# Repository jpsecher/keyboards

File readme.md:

# Custom Keyboard

Goals
- Good ergonomics
- Good for programming
- No drivers
- Configurable
- Use standard components where possible

On the ergonomics side, the initial design will be a pseudo-split staggered-column because it follows the natural physiology of the hands, and because I only need to make one or two for myself.  I want to make a PCB for the keyboard, so it seems to convoluted to go all the way to curved surfaces (eg. wells).  With a PCB, I can also support hot-swappable keys, which makes it possible to try out different spring weights for the individual fingers (like the [Absolem](https://zealot.hu/absolem/)).  And no stabilisers should be needed because the keys should just be where your finger naturally land, and therefore there should be no need for large 2U keys.  For the thumb keys, size 1.5U is probably sufficient.

Keys that need to be hold down while pressing other keys should only be operated by strong fingers.  So all modifier keys and layer shifting should probably be in the thumbs area, where it will be most comfortable to hold down a keys (as opposed to tapping the key).  But some modifier keys need to be hold down together, so these modifiers then need to be on opposite sides, using both thumbs at the same time.  

Good ergonomics with no curvatures then means that the number of keys must be limited to avoid stretching the fingers too much.  Which means that the keyboard needs to have several layers to accommodate all the ASCII characters used in programming, as well as the various European letters I use daily.  I am toying with the idea of using the thumb keys exclusively for layer-shift and control keys.

The keyboard should use standard hot-swappable Cherry MX keys.  And to ease experimentation, I will start out with DSA profile key caps.

## Layers

Contexts:

  1.  Programming (standard languages) in non-modal text editor.
  1.  Documentation (Markdown) in non-modal editor.
  1.  Terminal (shell) operations.
  1.  Window manager navigation.
  1.  Music control (easy identification of Play/Pause key at a glance)

And:

- Function keys are important in many of the applications I use.
- Editors usually inserts ending parenthesis/brace/bracket automatically.
- I don't care about RGB LEDs, as long as I can turn them off.
- I occasionally use Nordic/German/Greek letters when writing text.
- I want modifiers and layer keys on thumbs, and they should stay in the same place as much as possible.

Also, I prefer that each group of keys follow the traditional QWERTY layout, simply because it makes switching between keyboards less stressful.

## Keyboards in this repository

- [Acacia](acacia/): a pseudo-split 40 key column-staggered keyboard

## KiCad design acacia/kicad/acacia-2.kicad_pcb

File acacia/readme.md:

# Acacia keyboard

A custom built mechanical keyboard with just 38 keys plus two extra media keys.

The [layout](acacia.pdf) uses three layers.  One for alphas, one for navigation/function keys, and one for symbols/numpad.

The thumb home keys double as layer switches and tab/space.  The lower thumb keys are one-shot shift keys.

The Escape key is a [Layer Lock](https://getreuer.info/posts/keyboards/layer-lock) on both upper layers, which eliminates the strain of holding down the thumb for prolonged navigation and number punching.  And it makes it possible to move one hand to a trackball while using the other hand for mouse buttons.

The lower home row (Z, X, C, V) doubles as modifiers (AltGr, GUI, Alt, Control), and these functions are mirrored on the other hand (M, comma, period, quote).  This mirroring of modifiers is carried through on both other layers.

If used on macOS, then the Control and GUI (Command) keys should be swapped at the OS level.

As seen on the picture, the current layout for the alphas is [Minimak-6](http://www.minimak.org/), and it works very well with the already relocated T and Y keys on Acacia.  It is pretty close to standard QWERTY, so changing between the two should not be a problem.

## Improvements

- Remove the now unused lower thumb keys.
- Adjust the thumb keys slightly to make sure that key caps of any reasonable size do not collide.  Also, the thumb home key could be a little less tilted, and the whole bock moved a little further towards the middle.
- Align Q and P keys with ring finger use (instead of pinky use), or simply tilt the pinky columns the same as the ring finger column.
- Include a trackball (as alluded to in the pictures).  Unfortunately the ATmega32U2 used in the build does not have built-in I2C communication, so unless the controller is upgraded to eg. ATmega32U4, the communication has to be done brute-force through some of the five unused GPIO pins.
- Make a proper (wooden?) case.
- Shielding for the PCB.
- Layer status output, eg. through LEDs.

## Alternatives

- After finishing the prototypes, I discovered this repo: https://github.com/AlaaSaadAbdo/battoota/

## Version 2

The TM040040 trackpad needs the R1 (470k) resistor removed to use I2C and the R7 (0?) & R8 (0?) resistors removed for 5V.  The flex cable needed is 05-12-D-0050-A or another cable with contacts on oposite sides.

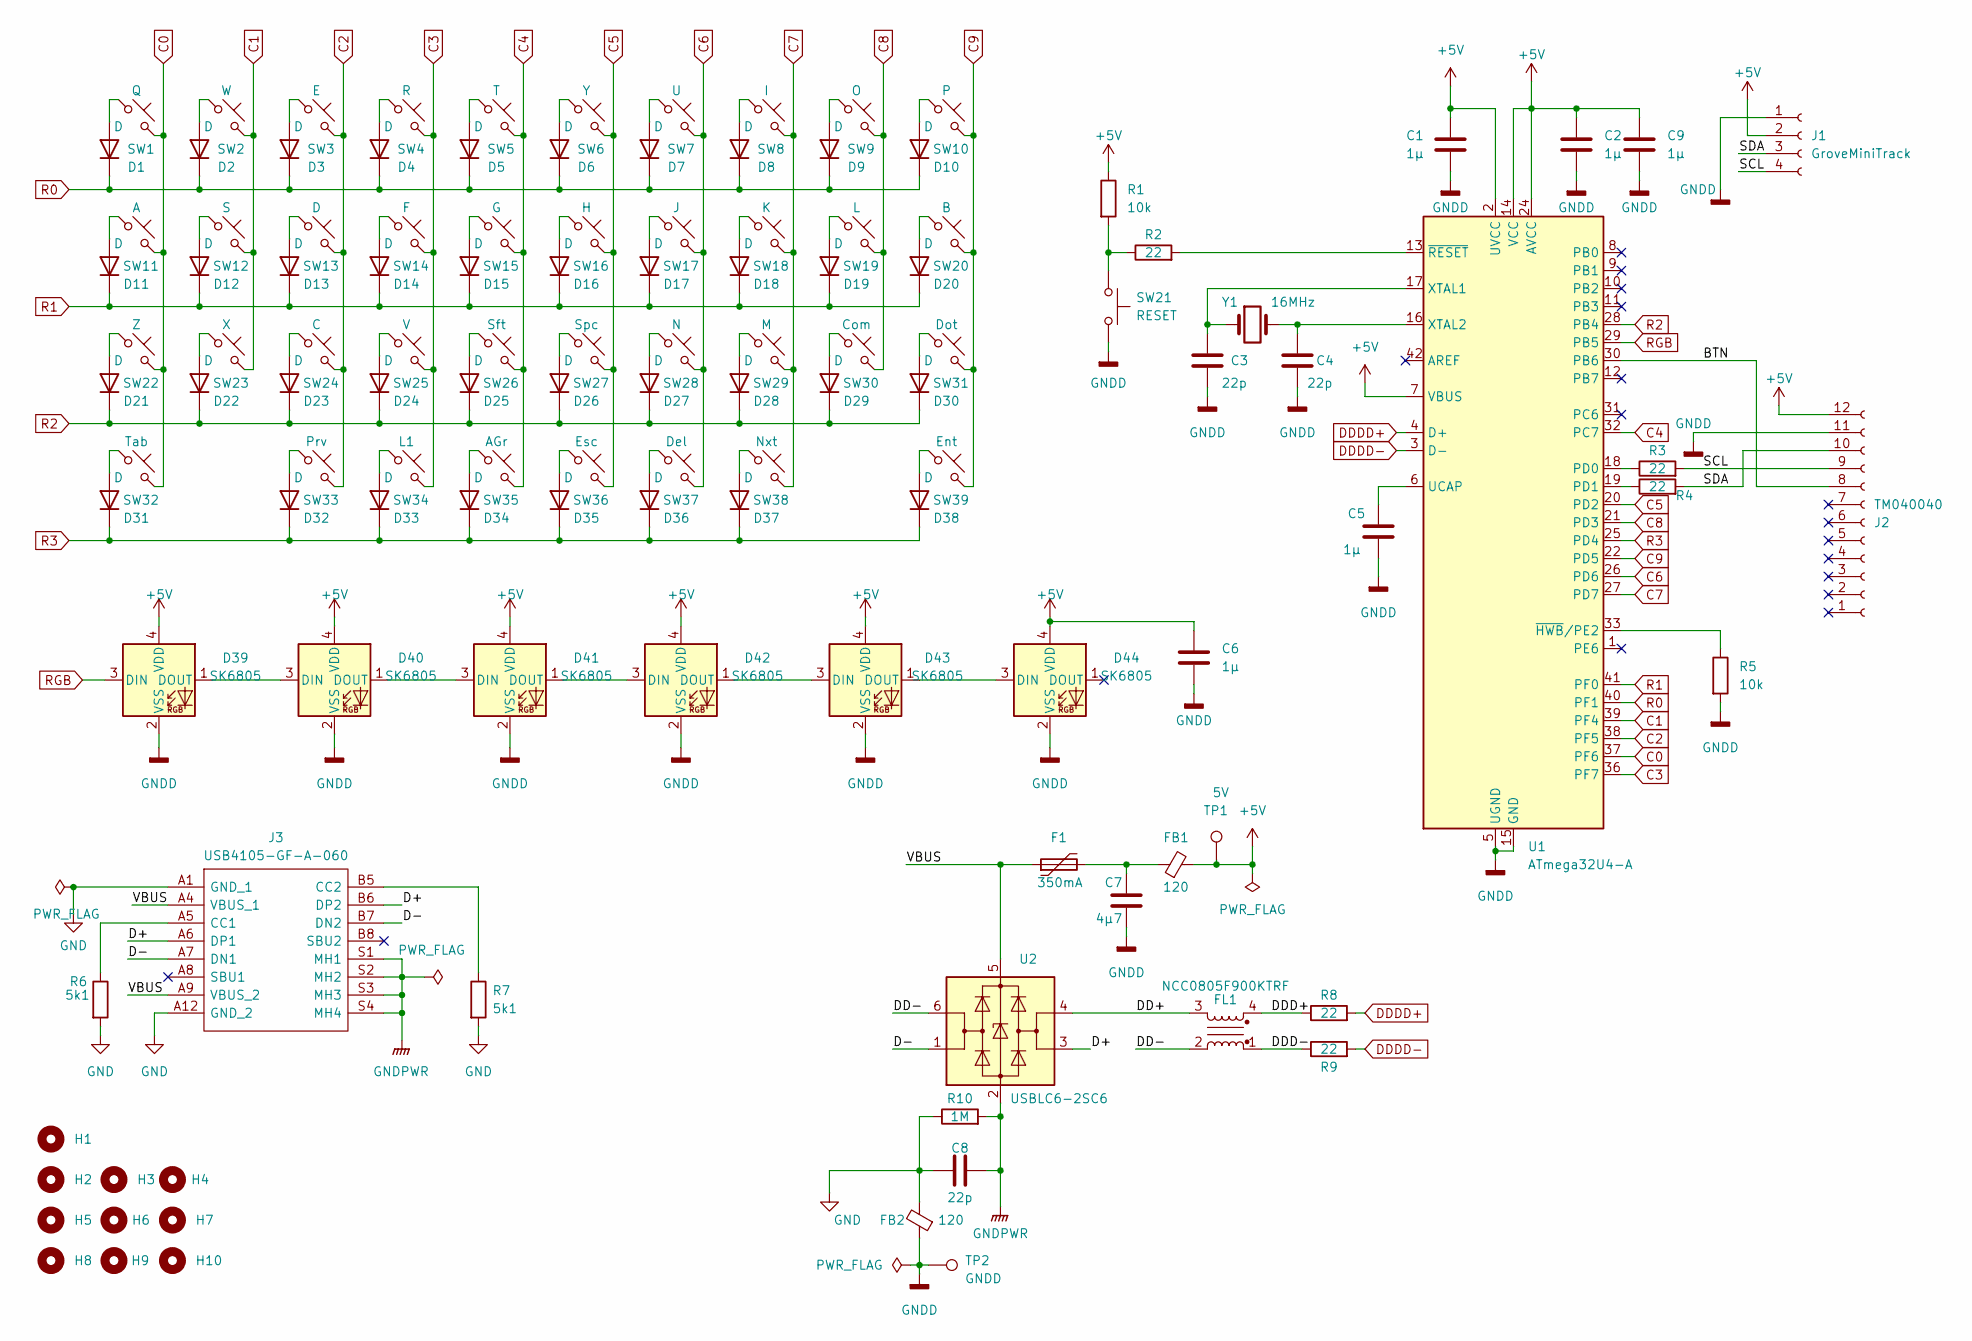
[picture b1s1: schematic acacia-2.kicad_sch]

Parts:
C1: 1µ; C_1206_3216Metric_Pad1.33x1.80mm_HandSolder
C2, C5, C6, C9: 1µ; C_0805_2012Metric_Pad1.18x1.45mm_HandSolder
C3, C4, C8: 22p; C_0805_2012Metric_Pad1.18x1.45mm_HandSolder
C7: 4µ7; C_0805_2012Metric_Pad1.18x1.45mm_HandSolder
D1, D2, D3, D4, D5, D6, D7, D8, D9, D10, D11, D12, D13, D14, D15, D16, D17, D18, D19, D20, D21, D22, D23, D24, D25, D26, D27, D28, D29, D30, D31, D32, D33, D34, D35, D36, D37, D38: D; D_0805_2012Metric_Pad1.15x1.40mm_HandSolder
D39, D40, D41, D42, D43, D44: SK6805; LED_SK6812_EC15_1.5x1.5mm
F1: 350mA; R_1206_3216Metric_Pad1.30x1.75mm_HandSolder
FB1, FB2: 120; R_0805_2012Metric_Pad1.20x1.40mm_HandSolder
FL1: NCC0805F900KTRF; L_CommonModeChoke_Coilcraft_0805USB
H1, H2, H3, H4, H5, H6, H7, H8, H9, H10: MountingHole; MountingHole_3.2mm_M3
J1: GroveMiniTrack; JST_XA_B04B-XASK-1-A_1x04_P2.50mm_Vertical
J2: TM040040; Hirose_FH12-12S-0.5SH_1x12-1MP_P0.50mm_Horizontal
J3: USB4105-GF-A-060; GCT_USB4105-GF-A; Mouser Part Number 640-USB4500030A
R1, R5: 10k; R_0805_2012Metric_Pad1.20x1.40mm_HandSolder
R2, R3, R4, R8, R9: 22; R_0805_2012Metric_Pad1.20x1.40mm_HandSolder
R6, R7: 5k1; R_0805_2012Metric_Pad1.20x1.40mm_HandSolder
R10: 1M; R_0805_2012Metric_Pad1.20x1.40mm_HandSolder
SW1: Q; MX-Hotswap-1U
SW2: W; MX-Hotswap-1U
SW3: E; MX-Hotswap-1U
SW4: R; MX-Hotswap-1U
SW5: T; MX-Hotswap-1U
SW6: Y; MX-Hotswap-1U
SW7: U; MX-Hotswap-1U
SW8: I; MX-Hotswap-1U
SW9: O; MX-Hotswap-1U
SW10: P; MX-Hotswap-1U
SW11: A; MX-Hotswap-1U
SW12: S; MX-Hotswap-1U
SW13: D; MX-Hotswap-1U
SW14: F; MX-Hotswap-1U
SW15: G; MX-Hotswap-1U
SW16: H; MX-Hotswap-1U
SW17: J; MX-Hotswap-1U
SW18: K; MX-Hotswap-1U
SW19: L; MX-Hotswap-1U
SW20: B; MX-Hotswap-1U
SW21: RESET; SW_SPST_EVQQ2
SW22: Z; MX-Hotswap-1U
SW23: X; MX-Hotswap-1U
SW24: C; MX-Hotswap-1U
SW25: V; MX-Hotswap-1U
SW26: Sft; MX-Hotswap-1.5U
SW27: Spc; MX-Hotswap-1.5U
SW28: N; MX-Hotswap-1U
SW29: M; MX-Hotswap-1U
SW30: Com; MX-Hotswap-1U
SW31: Dot; MX-Hotswap-1U
SW32: Tab; MX-Hotswap-1.5U
SW33: Prv; MX-Hotswap-1.5U
SW34: L1; MX-Hotswap-1U
SW35: AGr; MX-Hotswap-1.5U
SW36: Esc; MX-Hotswap-1.5U
SW37: Del; MX-Hotswap-1U
SW38: Nxt; MX-Hotswap-1.5U
SW39: Ent; MX-Hotswap-1.5U
TP1: 5V; TestPoint_Pad_D1.5mm
TP2: GNDD; TestPoint_Pad_D1.5mm
U1: ATmega32U4-A; TQFP-44_10x10mm_P0.8mm
U2: USBLC6-2SC6; SOT-23-6
Y1: 16MHz; Crystal_SMD_HC49-SD

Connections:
+5V: C1.1, C2.1, C6.1, C9.1, D39.4 (VDD), D40.4 (VDD), D41.4 (VDD), D42.4 (VDD), D43.4 (VDD), D44.4 (VDD), FB1.2, J1.2, J2.12, R1.1, TP1.1, U1.2 (UVCC), U1.7 (VBUS), U1.14 (VCC), U1.24 (AVCC), U1.34 (VCC), U1.44 (AVCC)
/BTN: J2.8, U1.30 (PB6)
/D+: J3.A6 (DP1), J3.B6 (DP2), U2.3 (I/O2)
/D-: J3.A7 (DN1), J3.B7 (DN2), U2.1 (I/O1)
/DD+: FL1.3, U2.4 (I/O2)
/DD-: FL1.2, U2.6 (I/O1)
/DDD+: FL1.4, R8.1
/DDD-: FL1.1, R9.1
/SCL: J1.4, J2.9, R3.2
/SDA: J1.3, J2.10, R4.2
/VBUS: F1.1, J3.A4 (VBUS_1), J3.A9 (VBUS_2), U2.5 (VBUS)
C0: SW1.2, SW11.2, SW22.2, SW32.2, U1.37 (PF6)
C1: SW2.2, SW12.2, SW23.2, U1.39 (PF4)
C2: SW3.2, SW13.2, SW24.2, SW33.2, U1.38 (PF5)
C3: SW4.2, SW14.2, SW25.2, SW34.2, U1.36 (PF7)
C4: SW5.2, SW15.2, SW26.2, SW35.2, U1.32 (PC7)
C5: SW6.2, SW16.2, SW27.2, SW36.2, U1.20 (PD2)
C6: SW7.2, SW17.2, SW28.2, SW37.2, U1.26 (PD6)
C7: SW8.2, SW18.2, SW29.2, SW38.2, U1.27 (PD7)
C8: SW9.2, SW19.2, SW30.2, U1.21 (PD3)
C9: SW10.2, SW20.2, SW31.2, SW39.2, U1.22 (PD5)
DDDD+: R8.2, U1.4 (D+)
DDDD-: R9.2, U1.3 (D-)
GND: C8.1, FB2.2, J3.A1 (GND_1), J3.A12 (GND_2), R6.2, R7.2, R10.1
GNDD: C1.2, C2.2, C3.2, C4.2, C5.2, C6.2, C7.1, C9.2, D39.2 (VSS), D40.2 (VSS), D41.2 (VSS), D42.2 (VSS), D43.2 (VSS), D44.2 (VSS), FB2.1, J1.1, J2.11, R5.2, SW21.2, TP2.1, U1.5 (UGND), U1.15 (GND), U1.23 (GND), U1.35 (GND), U1.43 (GND)
GNDPWR: C8.2, J3.S1 (MH1), J3.S2 (MH2), J3.S3 (MH3), J3.S4 (MH4), R10.2, U2.2 (GND)
unnamed: C7.2, F1.2, FB1.1
unnamed: D1.2 (A), SW1.1
unnamed: D2.2 (A), SW2.1
unnamed: D3.2 (A), SW3.1
unnamed: D4.2 (A), SW4.1
unnamed: D5.2 (A), SW5.1
unnamed: D6.2 (A), SW6.1
unnamed: D7.2 (A), SW7.1
unnamed: D8.2 (A), SW8.1
unnamed: D9.2 (A), SW9.1
unnamed: D10.2 (A), SW10.1
unnamed: D11.2 (A), SW11.1
unnamed: D12.2 (A), SW12.1
unnamed: D13.2 (A), SW13.1
unnamed: D14.2 (A), SW14.1
unnamed: D15.2 (A), SW15.1
unnamed: D16.2 (A), SW16.1
unnamed: D17.2 (A), SW17.1
unnamed: D18.2 (A), SW18.1
unnamed: D19.2 (A), SW19.1
unnamed: D20.2 (A), SW20.1
unnamed: D21.2 (A), SW22.1
unnamed: D22.2 (A), SW23.1
unnamed: D23.2 (A), SW24.1
unnamed: D24.2 (A), SW25.1
unnamed: D25.2 (A), SW26.1
unnamed: D26.2 (A), SW27.1
unnamed: D27.2 (A), SW28.1
unnamed: D28.2 (A), SW29.1
unnamed: D29.2 (A), SW30.1
unnamed: D30.2 (A), SW31.1
unnamed: D31.2 (A), SW32.1
unnamed: D32.2 (A), SW33.1
unnamed: D33.2 (A), SW34.1
unnamed: D34.2 (A), SW35.1
unnamed: D35.2 (A), SW36.1
unnamed: D36.2 (A), SW37.1
unnamed: D37.2 (A), SW38.1
unnamed: D38.2 (A), SW39.1
unnamed: D39.1 (DOUT), D40.3 (DIN)
unnamed: D40.1 (DOUT), D41.3 (DIN)
unnamed: D41.1 (DOUT), D42.3 (DIN)
unnamed: D42.1 (DOUT), D43.3 (DIN)
unnamed: D43.1 (DOUT), D44.3 (DIN)
unnamed: J3.A5 (CC1), R6.1
unnamed: J3.B5 (CC2), R7.1
unnamed: R1.2, R2.1, SW21.1
unnamed: R3.1, U1.18 (PD0)
unnamed: R4.1, U1.19 (PD1)
unnamed: C5.1, U1.6 (UCAP)
unnamed: C3.1, U1.17 (XTAL1), Y1.1
unnamed: C4.1, U1.16 (XTAL2), Y1.2
unnamed: R5.1, U1.33 (~HWB/PE2)
unnamed: R2.2, U1.13 (~RESET)
R0: D1.1 (K), D2.1 (K), D3.1 (K), D4.1 (K), D5.1 (K), D6.1 (K), D7.1 (K), D8.1 (K), D9.1 (K), D10.1 (K), U1.40 (PF1)
R1: D11.1 (K), D12.1 (K), D13.1 (K), D14.1 (K), D15.1 (K), D16.1 (K), D17.1 (K), D18.1 (K), D19.1 (K), D20.1 (K), U1.41 (PF0)
R2: D21.1 (K), D22.1 (K), D23.1 (K), D24.1 (K), D25.1 (K), D26.1 (K), D27.1 (K), D28.1 (K), D29.1 (K), D30.1 (K), U1.28 (PB4)
R3: D31.1 (K), D32.1 (K), D33.1 (K), D34.1 (K), D35.1 (K), D36.1 (K), D37.1 (K), D38.1 (K), U1.25 (PD4)
RGB: D39.3 (DIN), U1.29 (PB5)

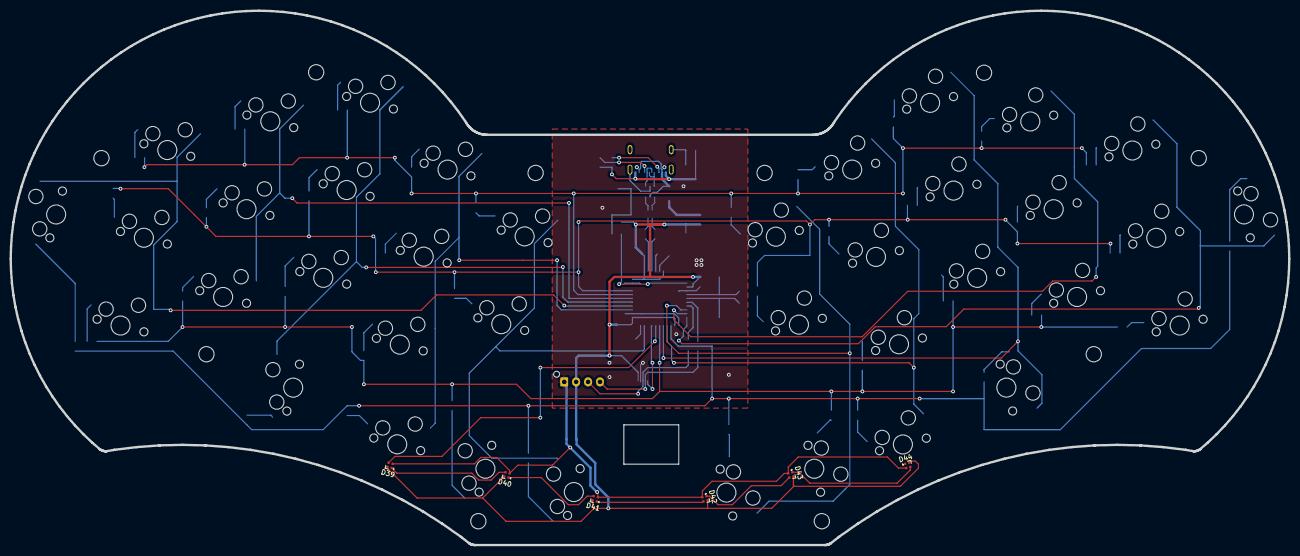
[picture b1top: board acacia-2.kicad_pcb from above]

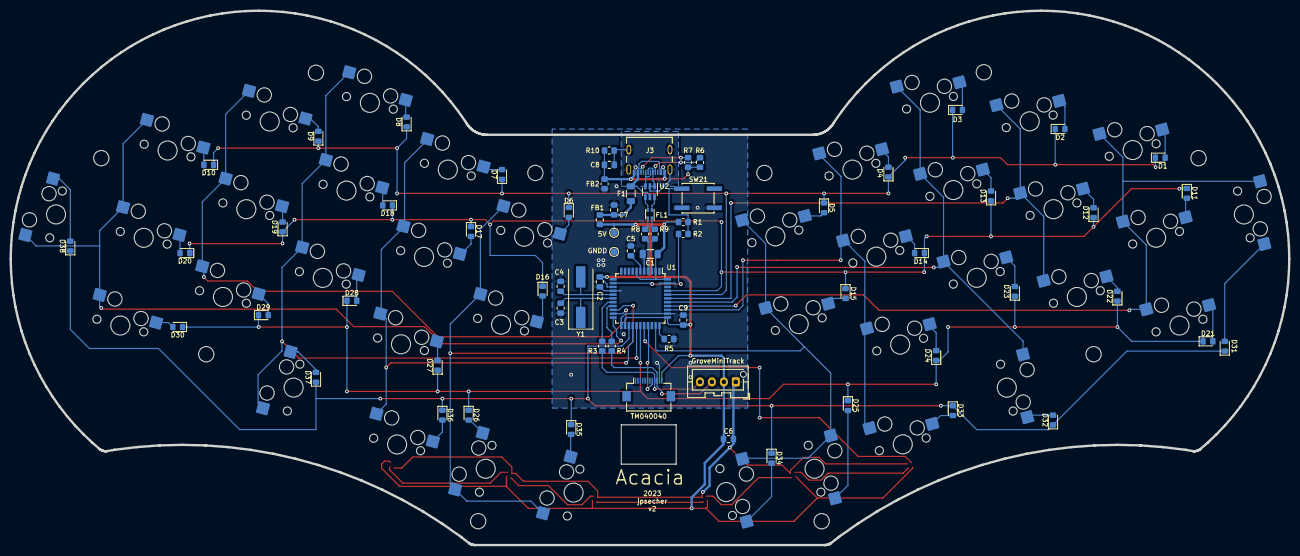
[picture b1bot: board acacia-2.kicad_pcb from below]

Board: 2 copper layers, 268.0 x 112.0 mm, 124 parts (80 on the bottom side), 85 nets.

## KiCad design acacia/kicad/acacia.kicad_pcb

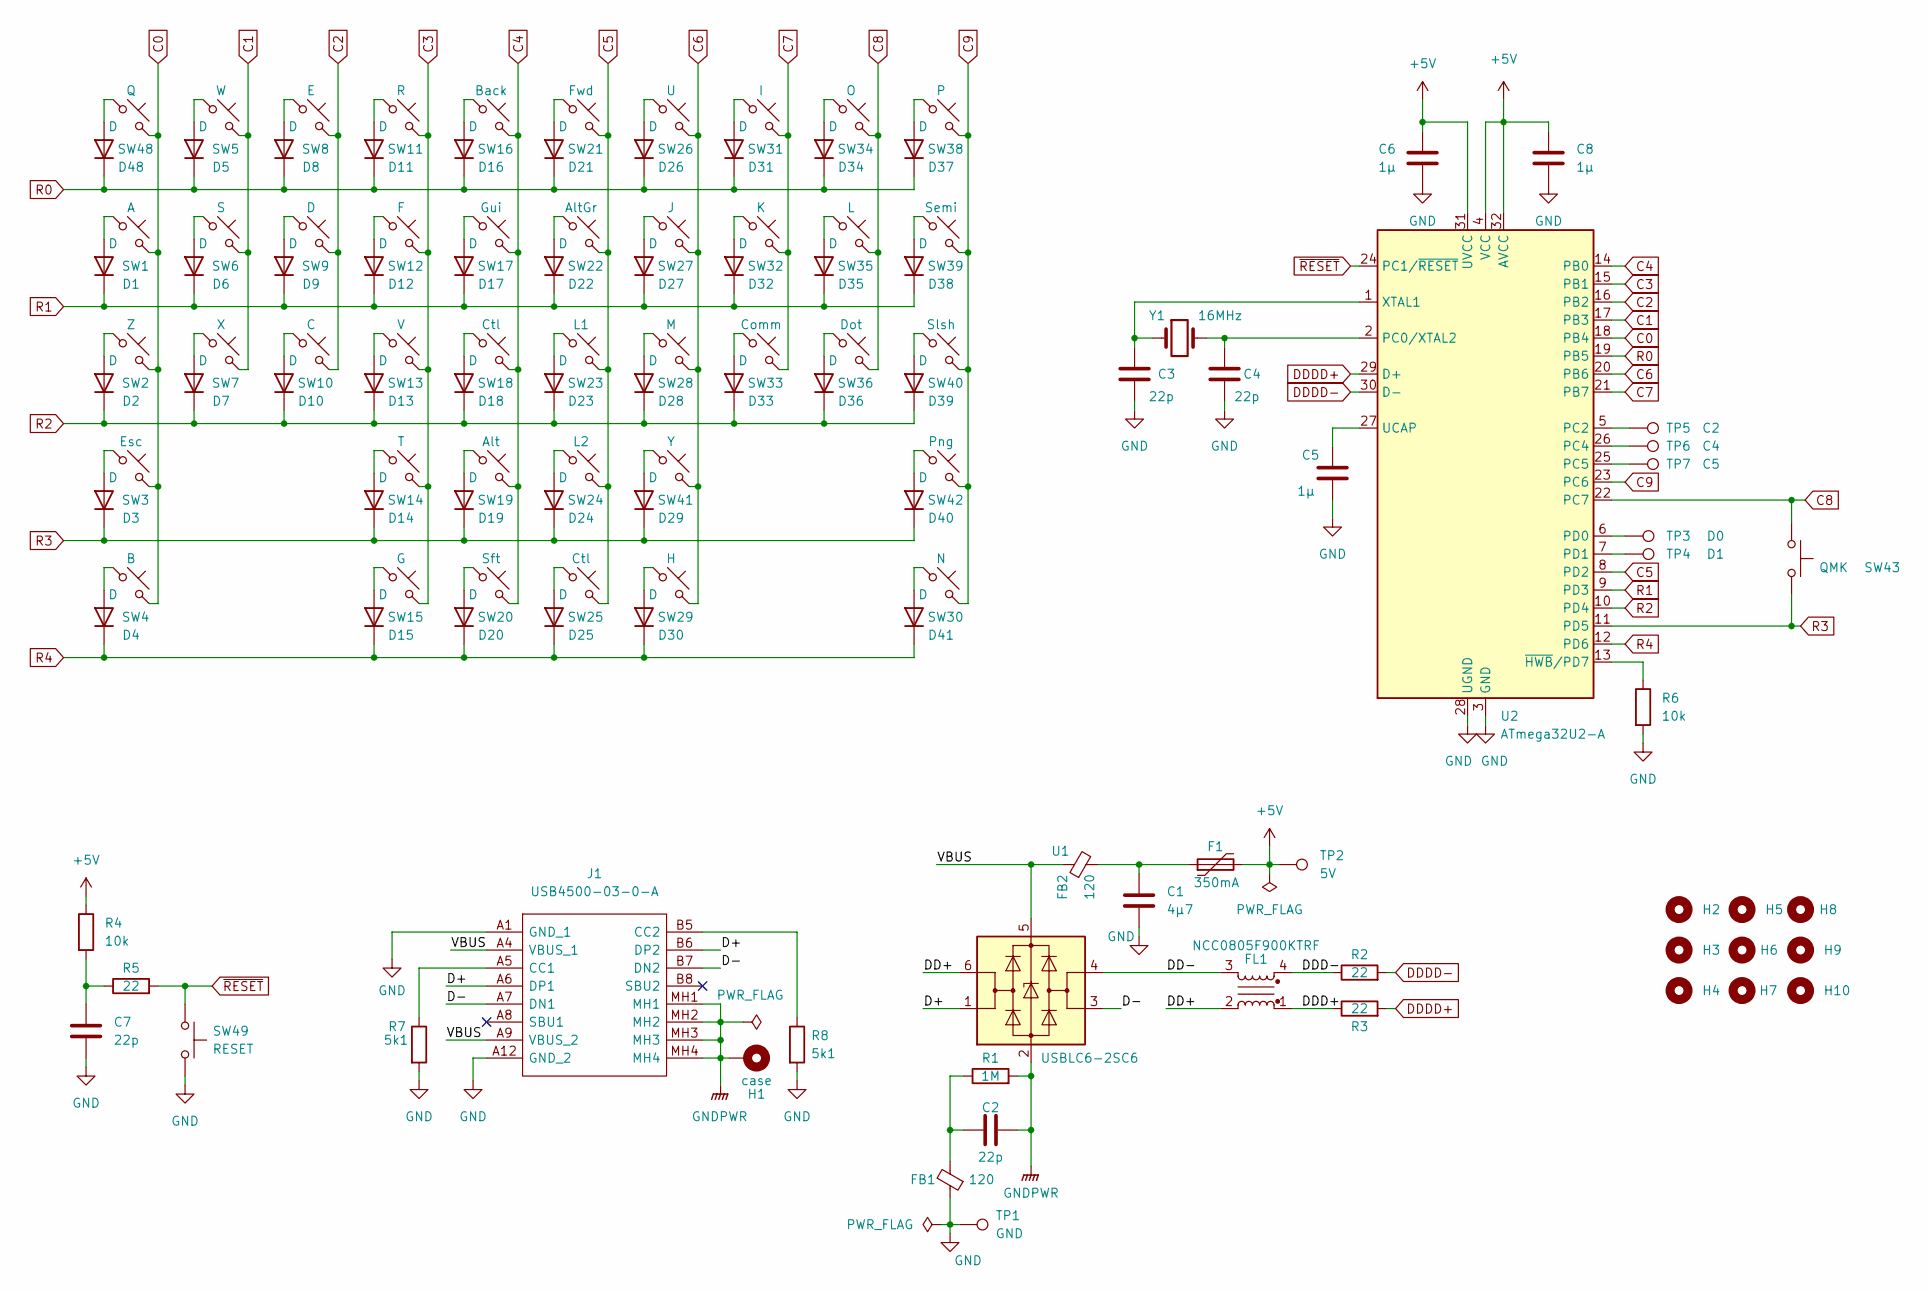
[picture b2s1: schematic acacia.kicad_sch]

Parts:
C1: 4µ7; C_0805_2012Metric_Pad1.18x1.45mm_HandSolder
C2, C3, C4, C7: 22p; C_0805_2012Metric_Pad1.18x1.45mm_HandSolder
C5, C8: 1µ; C_0805_2012Metric_Pad1.18x1.45mm_HandSolder
C6: 1µ; C_1206_3216Metric_Pad1.33x1.80mm_HandSolder
D1, D2, D3, D4, D5, D6, D7, D8, D9, D10, D11, D12, D13, D14, D15, D16, D17, D18, D19, D20, D21, D22, D23, D24, D25, D26, D27, D28, D29, D30, D31, D32, D33, D34, D35, D36, D37, D38, D39, D40, D41, D48: D; D_0805_2012Metric_Pad1.15x1.40mm_HandSolder
F1: 350mA; R_1210_3225Metric_Pad1.30x2.65mm_HandSolder
FB1, FB2: 120; R_0805_2012Metric_Pad1.20x1.40mm_HandSolder
FL1: NCC0805F900KTRF; L_CommonModeChoke_Coilcraft_0805USB
H1: case; MountingHole_3.2mm_M3_ISO14580_Pad
H2, H3, H4, H5, H6, H7, H8, H9, H10: MountingHole; MountingHole_3.2mm_M3
J1: USB4500-03-0-A; USB4500030A; Mouser Part Number 640-USB4500030A
R1: 1M; R_0805_2012Metric_Pad1.20x1.40mm_HandSolder
R2, R3, R5: 22; R_0805_2012Metric_Pad1.20x1.40mm_HandSolder
R4, R6: 10k; R_0805_2012Metric_Pad1.20x1.40mm_HandSolder
R7, R8: 5k1; R_0805_2012Metric_Pad1.20x1.40mm_HandSolder
SW1: A; MX-Hotswap-1U
SW2: Z; MX-Hotswap-1U
SW3: Esc; MX-Hotswap-1U
SW4: B; MX-Hotswap-1U
SW5: W; MX-Hotswap-1U
SW6: S; MX-Hotswap-1U
SW7: X; MX-Hotswap-1U
SW8: E; MX-Hotswap-1U
SW9: D; MX-Hotswap-1U
SW10: C; MX-Hotswap-1U
SW11: R; MX-Hotswap-1U
SW12: F; MX-Hotswap-1U
SW13: V; MX-Hotswap-1U
SW14: T; MX-Hotswap-1U
SW15: G; MX-Hotswap-1U
SW16: Back; MX-Hotswap-1U
SW17: Gui; MX-Hotswap-1U
SW18: Ctl; MX-Hotswap-1.5U
SW19: Alt; MX-Hotswap-1.25U
SW20: Sft; MX-Hotswap-1U
SW21: Fwd; MX-Hotswap-1U
SW22: AltGr; MX-Hotswap-1U
SW23: L1; MX-Hotswap-1.5U
SW24: L2; MX-Hotswap-1.25U
SW25: Ctl; MX-Hotswap-1U
SW26: U; MX-Hotswap-1U
SW27: J; MX-Hotswap-1U
SW28: M; MX-Hotswap-1U
SW29: H; MX-Hotswap-1U
SW30: N; MX-Hotswap-1U
SW31: I; MX-Hotswap-1U
SW32: K; MX-Hotswap-1U
SW33: Comm; MX-Hotswap-1U
SW34: O; MX-Hotswap-1U
SW35: L; MX-Hotswap-1U
SW36: Dot; MX-Hotswap-1U
SW38: P; MX-Hotswap-1U
SW39: Semi; MX-Hotswap-1U
SW40: Slsh; MX-Hotswap-1U
SW41: Y; MX-Hotswap-1U
SW42: Png; MX-Hotswap-1U
SW43: QMK; SW_SPST_EVQQ2
SW48: Q; MX-Hotswap-1U
SW49: RESET; SW_SPST_EVQQ2
TP1: GND; TestPoint_Pad_1.0x1.0mm
TP2: 5V; TestPoint_Pad_1.0x1.0mm
TP3: D0; TestPoint_Pad_1.0x1.0mm
TP4: D1; TestPoint_Pad_1.0x1.0mm
TP5: C2; TestPoint_Pad_1.0x1.0mm
TP6: C4; TestPoint_Pad_1.0x1.0mm
TP7: C5; TestPoint_Pad_1.0x1.0mm
U1: USBLC6-2SC6; SOT-23-6
U2: ATmega32U2-A; TQFP-32_7x7mm_P0.8mm
Y1: 16MHz; Crystal_SMD_HC49-SD

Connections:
+5V: C6.1, C8.1, F1.2, R4.1, TP2.1, U2.4 (VCC), U2.31 (UVCC), U2.32 (AVCC)
/D+: J1.A6 (DP1), J1.B6 (DP2), U1.1 (I/O1)
/D-: J1.A7 (DN1), J1.B7 (DN2), U1.3 (I/O2)
/DD+: FL1.2, U1.6 (I/O1)
/DD-: FL1.3, U1.4 (I/O2)
/DDD+: FL1.1, R3.1
/DDD-: FL1.4, R2.1
/VBUS: FB2.1, J1.A4 (VBUS_1), J1.A9 (VBUS_2), U1.5 (VBUS)
C0: SW1.2, SW2.2, SW3.2, SW4.2, SW48.2, U2.18 (PB4)
C1: SW5.2, SW6.2, SW7.2, U2.17 (PB3)
C2: SW8.2, SW9.2, SW10.2, U2.16 (PB2)
C3: SW11.2, SW12.2, SW13.2, SW14.2, SW15.2, U2.15 (PB1)
C4: SW16.2, SW17.2, SW18.2, SW19.2, SW20.2, U2.14 (PB0)
C5: SW21.2, SW22.2, SW23.2, SW24.2, SW25.2, U2.8 (PD2)
C6: SW26.2, SW27.2, SW28.2, SW29.2, SW41.2, U2.20 (PB6)
C7: SW31.2, SW32.2, SW33.2, U2.21 (PB7)
C8: SW34.2, SW35.2, SW36.2, SW43.1, U2.22 (PC7)
C9: SW30.2, SW38.2, SW39.2, SW40.2, SW42.2, U2.23 (PC6)
DDDD+: R3.2, U2.29 (D+)
DDDD-: R2.2, U2.30 (D-)
GND: C1.1, C3.2, C4.2, C5.2, C6.2, C7.2, C8.2, FB1.1, J1.A1 (GND_1), J1.A12 (GND_2), R6.2, R7.2, R8.2, SW49.2, TP1.1, U2.3 (GND), U2.28 (UGND)
GNDPWR: C2.2, H1.1, J1.MH1, J1.MH2, J1.MH3, J1.MH4, R1.2, U1.2 (GND)
unnamed: C1.2, F1.1, FB2.2
unnamed: C2.1, FB1.2, R1.1
unnamed: C3.1, U2.1 (XTAL1), Y1.1
unnamed: C4.1, U2.2 (PC0/XTAL2), Y1.2
unnamed: C5.1, U2.27 (UCAP)
unnamed: C7.1, R4.2, R5.1
unnamed: D1.2 (A), SW1.1
unnamed: D2.2 (A), SW2.1
unnamed: D3.2 (A), SW3.1
unnamed: D4.2 (A), SW4.1
unnamed: D5.2 (A), SW5.1
unnamed: D6.2 (A), SW6.1
unnamed: D7.2 (A), SW7.1
unnamed: D8.2 (A), SW8.1
unnamed: D9.2 (A), SW9.1
unnamed: D10.2 (A), SW10.1
unnamed: D11.2 (A), SW11.1
unnamed: D12.2 (A), SW12.1
unnamed: D13.2 (A), SW13.1
unnamed: D14.2 (A), SW14.1
unnamed: D15.2 (A), SW15.1
unnamed: D16.2 (A), SW16.1
unnamed: D17.2 (A), SW17.1
unnamed: D18.2 (A), SW18.1
unnamed: D19.2 (A), SW19.1
unnamed: D20.2 (A), SW20.1
unnamed: D21.2 (A), SW21.1
unnamed: D22.2 (A), SW22.1
unnamed: D23.2 (A), SW23.1
unnamed: D24.2 (A), SW24.1
unnamed: D25.2 (A), SW25.1
unnamed: D26.2 (A), SW26.1
unnamed: D27.2 (A), SW27.1
unnamed: D28.2 (A), SW28.1
unnamed: D29.2 (A), SW41.1
unnamed: D30.2 (A), SW29.1
unnamed: D31.2 (A), SW31.1
unnamed: D32.2 (A), SW32.1
unnamed: D33.2 (A), SW33.1
unnamed: D34.2 (A), SW34.1
unnamed: D35.2 (A), SW35.1
unnamed: D36.2 (A), SW36.1
unnamed: D37.2 (A), SW38.1
unnamed: D38.2 (A), SW39.1
unnamed: D39.2 (A), SW40.1
unnamed: D40.2 (A), SW42.1
unnamed: D41.2 (A), SW30.1
unnamed: D48.2 (A), SW48.1
unnamed: J1.A5 (CC1), R7.1
unnamed: J1.B5 (CC2), R8.1
unnamed: R6.1, U2.13 (~HWB/PD7)
unnamed: TP3.1, U2.6 (PD0)
unnamed: TP4.1, U2.7 (PD1)
unnamed: TP5.1, U2.5 (PC2)
unnamed: TP6.1, U2.26 (PC4)
unnamed: TP7.1, U2.25 (PC5)
R0: D5.1 (K), D8.1 (K), D11.1 (K), D16.1 (K), D21.1 (K), D26.1 (K), D31.1 (K), D34.1 (K), D37.1 (K), D48.1 (K), U2.19 (PB5)
R1: D1.1 (K), D6.1 (K), D9.1 (K), D12.1 (K), D17.1 (K), D22.1 (K), D27.1 (K), D32.1 (K), D35.1 (K), D38.1 (K), U2.9 (PD3)
R2: D2.1 (K), D7.1 (K), D10.1 (K), D13.1 (K), D18.1 (K), D23.1 (K), D28.1 (K), D33.1 (K), D36.1 (K), D39.1 (K), U2.10 (PD4)
R3: D3.1 (K), D14.1 (K), D19.1 (K), D24.1 (K), D29.1 (K), D40.1 (K), SW43.2, U2.11 (PD5)
R4: D4.1 (K), D15.1 (K), D20.1 (K), D25.1 (K), D30.1 (K), D41.1 (K), U2.12 (PD6)
~RESET: R5.2, SW49.1, U2.24 (PC1/~RESET)

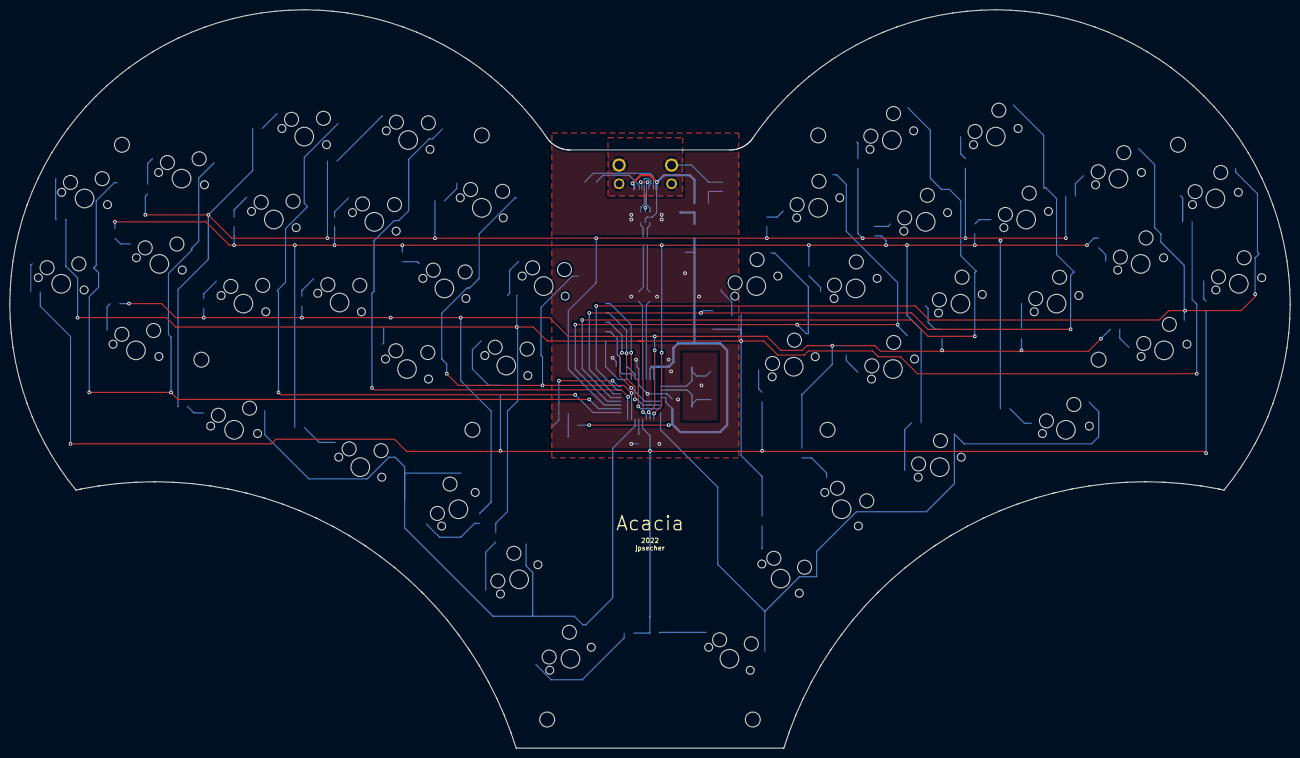
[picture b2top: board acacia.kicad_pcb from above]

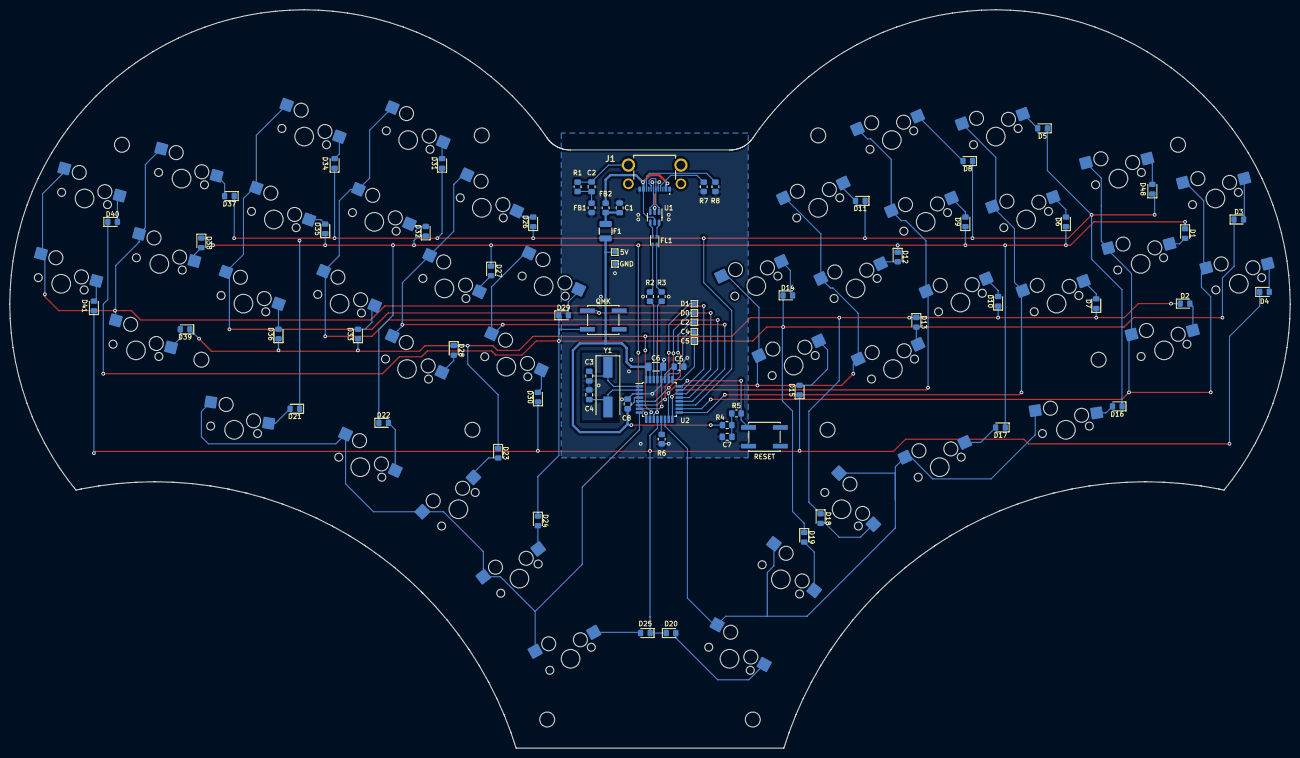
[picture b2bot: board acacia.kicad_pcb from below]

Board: 2 copper layers, 274.0 x 158.0 mm, 127 parts (75 on the bottom side), 84 nets.

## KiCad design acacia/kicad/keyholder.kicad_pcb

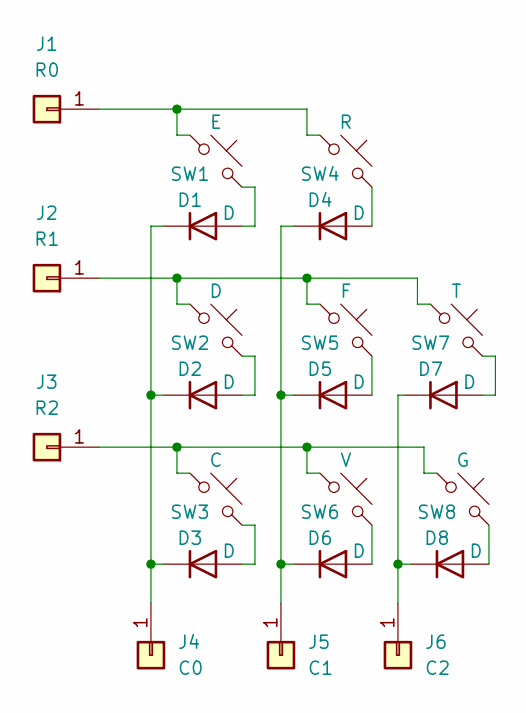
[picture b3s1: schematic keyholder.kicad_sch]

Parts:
D1, D2, D3, D4, D5, D6, D7, D8: D; D_0805_2012Metric_Pad1.15x1.40mm_HandSolder
J1: R0; Pin_D0.7mm_L6.5mm_W1.8mm_FlatFork
J2: R1; Pin_D0.7mm_L6.5mm_W1.8mm_FlatFork
J3: R2; Pin_D0.7mm_L6.5mm_W1.8mm_FlatFork
J4: C0; Pin_D0.7mm_L6.5mm_W1.8mm_FlatFork
J5: C1; Pin_D0.7mm_L6.5mm_W1.8mm_FlatFork
J6: C2; Pin_D0.7mm_L6.5mm_W1.8mm_FlatFork
SW1: E; MX-Hotswap-1U
SW2: D; MX-Hotswap-1U
SW3: C; MX-Hotswap-1U
SW4: R; MX-Hotswap-1U
SW5: F; MX-Hotswap-1U
SW6: V; MX-Hotswap-1U
SW7: T; MX-Hotswap-1U
SW8: G; MX-Hotswap-1U

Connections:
unnamed: D1.1 (K), D2.1 (K), D3.1 (K), J4.1
unnamed: D1.2 (A), SW1.2
unnamed: D2.2 (A), SW2.2
unnamed: D3.2 (A), SW3.2
unnamed: D4.1 (K), D5.1 (K), D6.1 (K), J5.1
unnamed: D4.2 (A), SW4.2
unnamed: D5.2 (A), SW5.2
unnamed: D6.2 (A), SW6.2
unnamed: D7.1 (K), D8.1 (K), J6.1
unnamed: D7.2 (A), SW7.2
unnamed: D8.2 (A), SW8.2
unnamed: J1.1, SW1.1, SW4.1
unnamed: J2.1, SW2.1, SW5.1, SW7.1
unnamed: J3.1, SW3.1, SW6.1, SW8.1

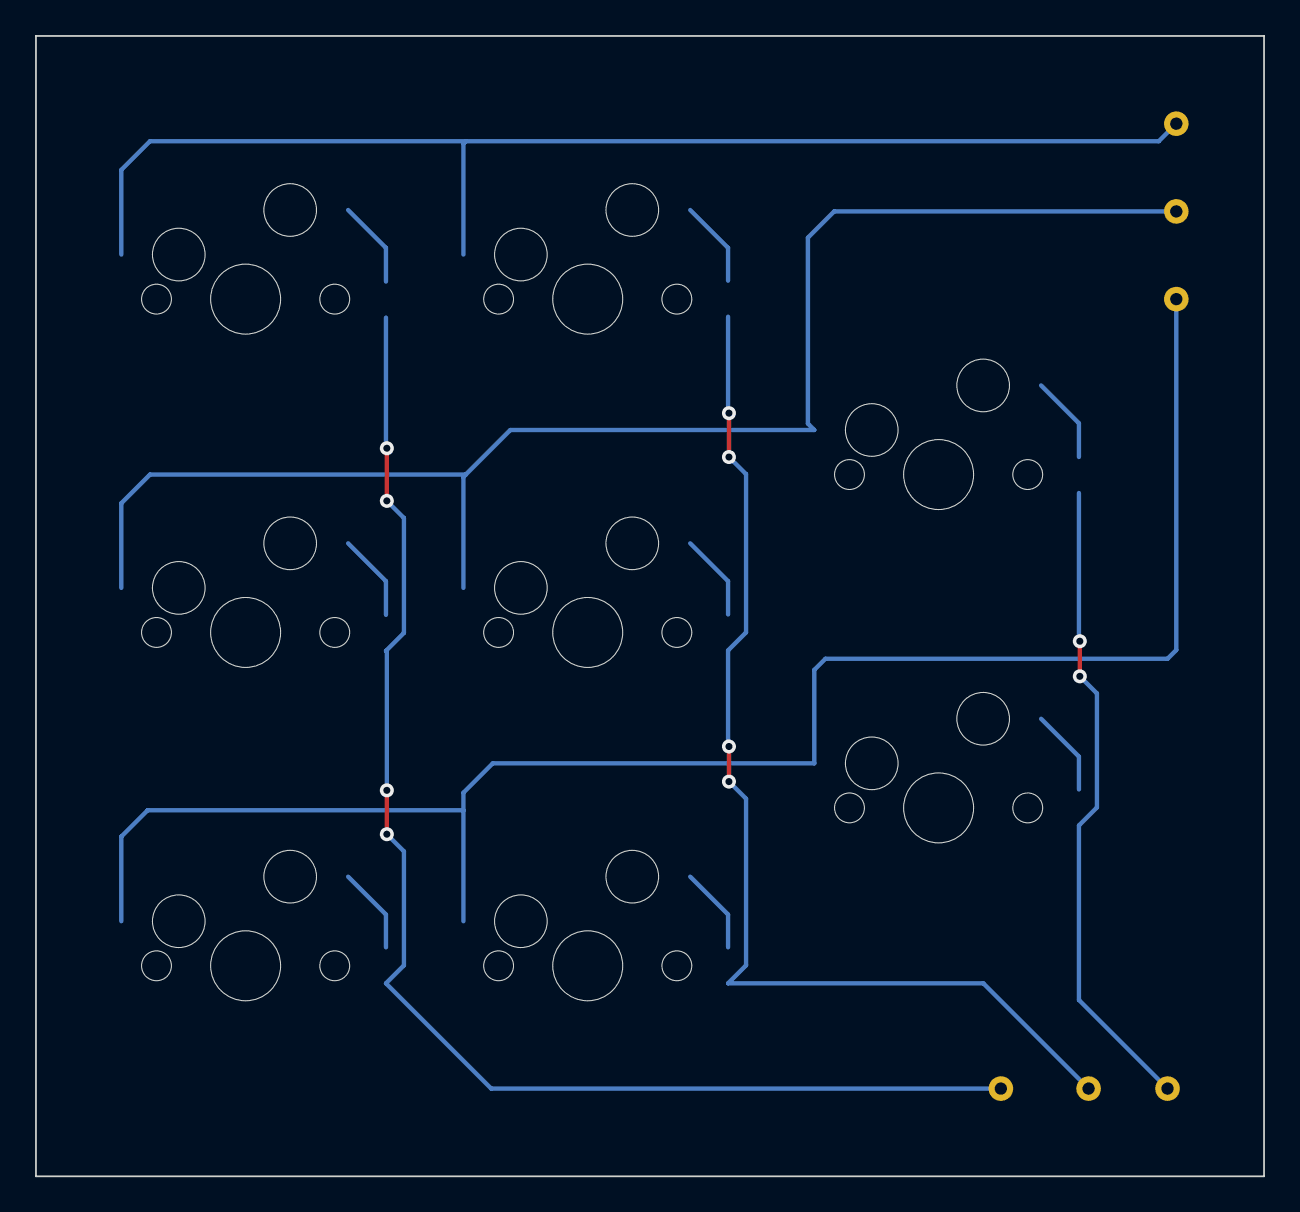
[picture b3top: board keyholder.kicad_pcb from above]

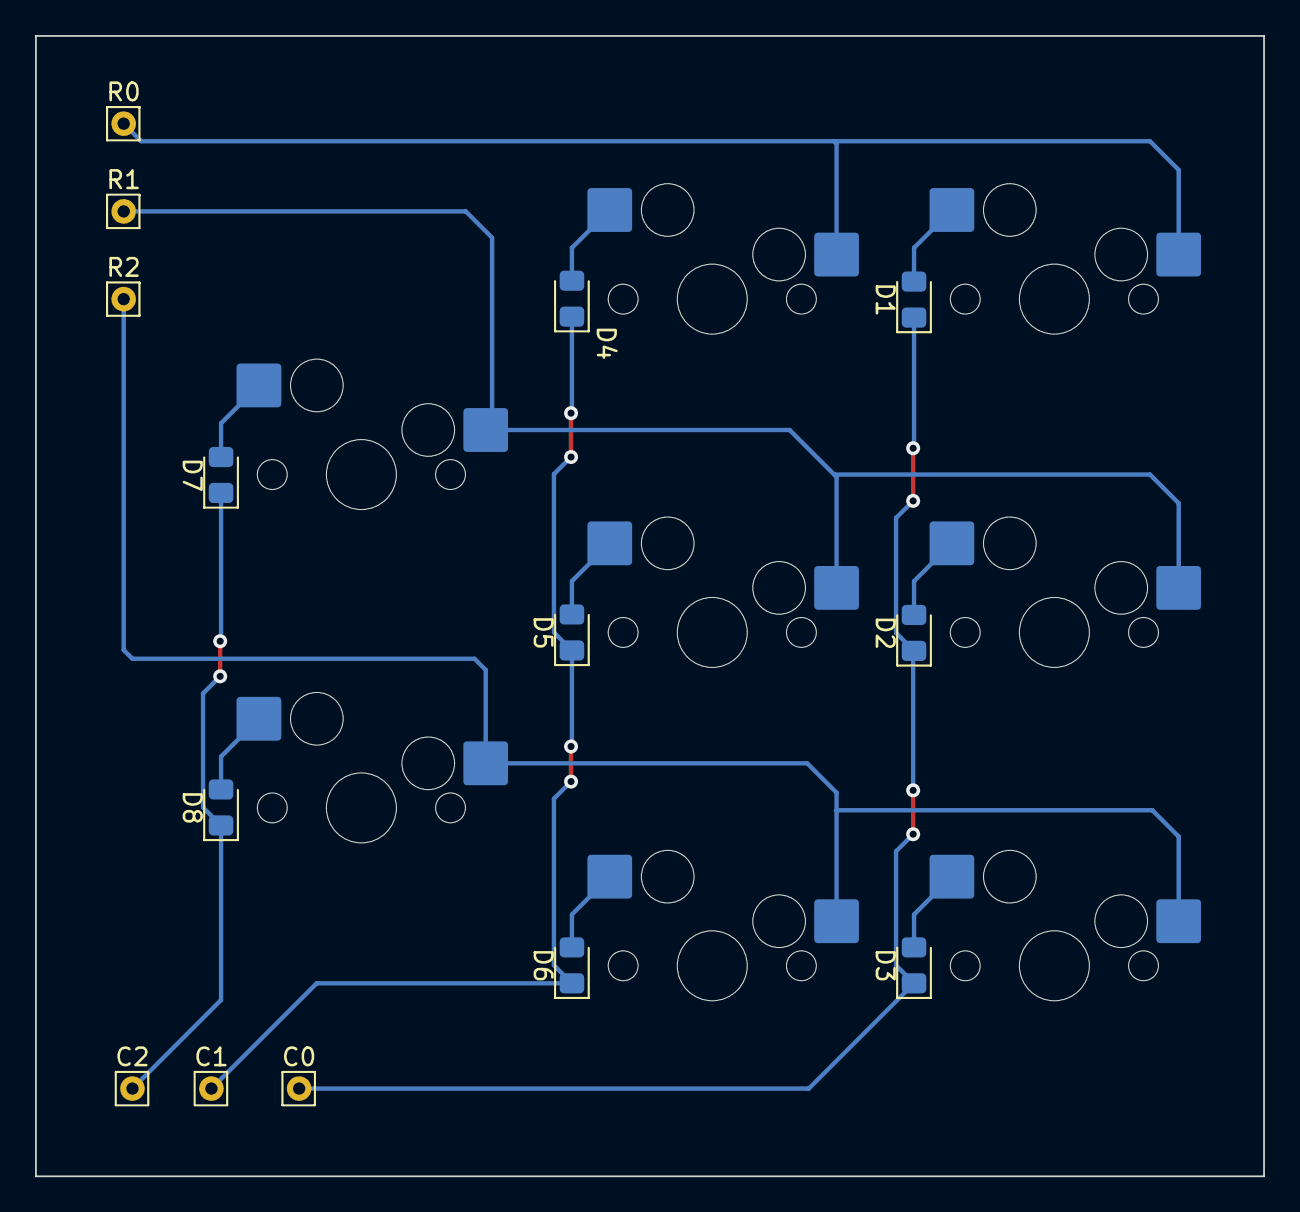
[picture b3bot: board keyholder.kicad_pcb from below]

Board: 2 copper layers, 70.0 x 65.0 mm, 22 parts (14 on the bottom side), 14 nets.
